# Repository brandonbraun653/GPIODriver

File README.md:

# GPIODriver

This project is intended to provide a low-cost USB tethered HW/SW solution for controlling a large amount of discrete IO
signals at standard aircraft voltage levels (28vdc). More will be added here as the project matures. Currently in the
prototyping phase for both the hardware and the software.

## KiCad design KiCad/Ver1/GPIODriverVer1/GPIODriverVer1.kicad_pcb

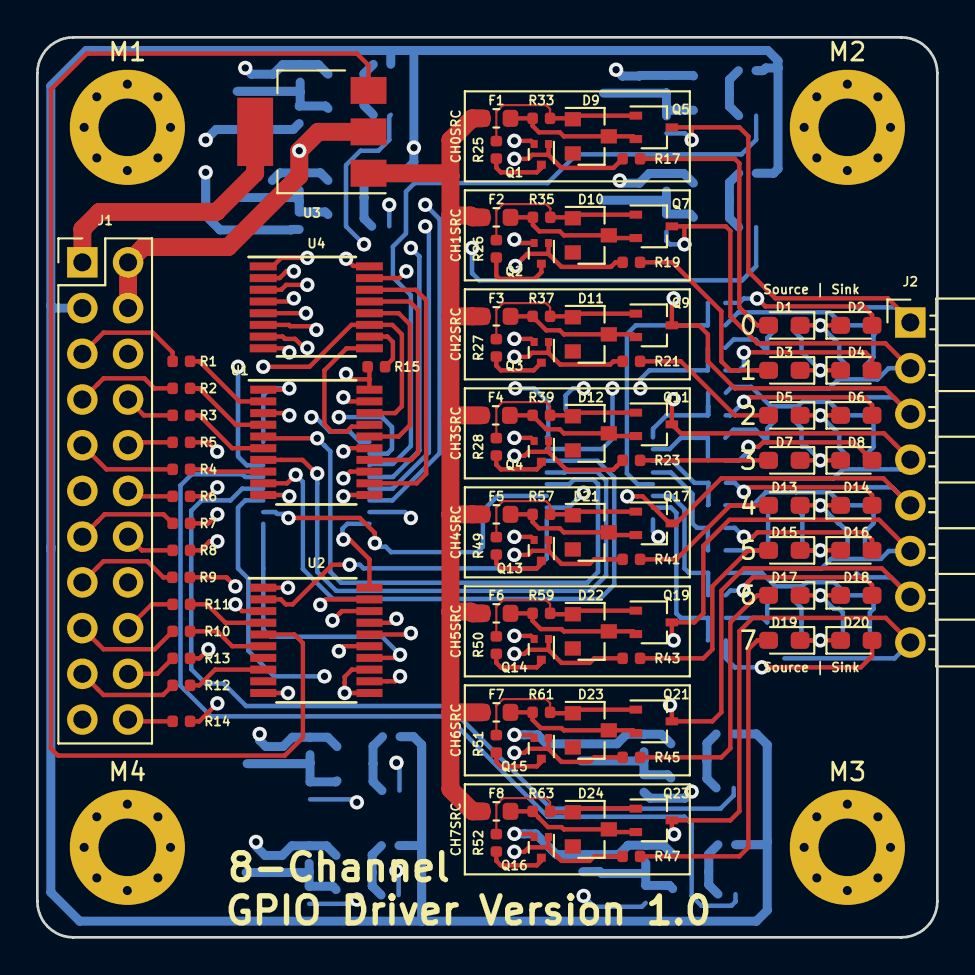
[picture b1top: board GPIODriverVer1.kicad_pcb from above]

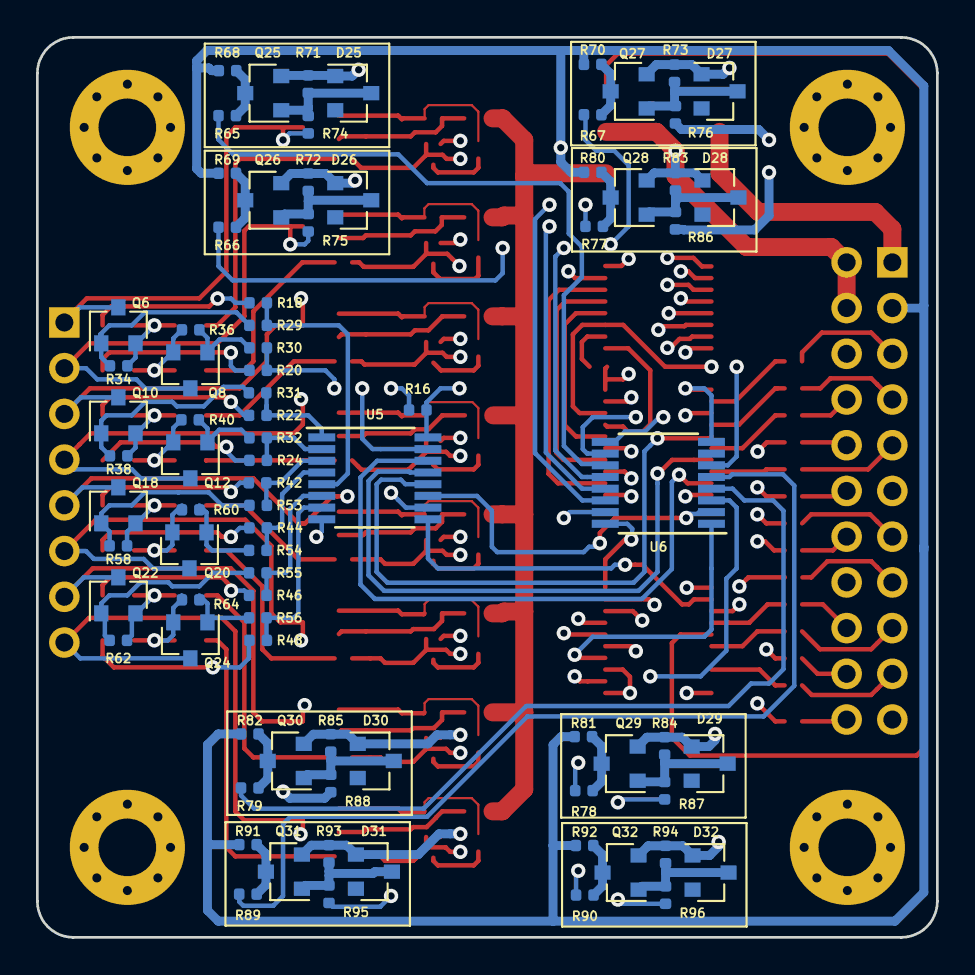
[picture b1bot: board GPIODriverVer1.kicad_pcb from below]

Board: 4 copper layers, 50.0 x 50.0 mm, 180 parts (83 on the bottom side), 144 nets.

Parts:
D1, D3, D5, D7, D13, D15, D17, D19: ActiveSource; D_0603_1608Metric_Pad1.05x0.95mm_HandSolder
D2, D4, D6, D8, D14, D16, D18, D20: ActiveSink; D_0603_1608Metric_Pad1.05x0.95mm_HandSolder
D9, D10, D11, D12, D21, D22, D23, D24, D25, D26, D27, D28, D29, D30, D31, D32: BZX84C12; D_SOT-23_ANK
F1, F2, F3, F4, F5, F6, F7, F8: C2Q300; R_0603_1608Metric
J1: Conn_01x22_Male; PinHeader_2x11_P2.54mm_Vertical
J2: GPIODriveOutputs; PinHeader_1x08_P2.54mm_Horizontal
M1, M2, M3, M4: MountingHole_3.2mm_M3_Pad_Via
Q1, Q2, Q3, Q4, Q13, Q14, Q15, Q16: DTC143EE; SOT-723
Q5, Q7, Q9, Q11, Q17, Q19, Q21, Q23: BSS84; SOT-323_SC-70
Q6, Q8, Q10, Q12, Q18, Q20, Q22, Q24, Q25, Q26, Q27, Q28, Q29, Q30, Q31, Q32: 2N7002; SOT-23
R1, R2, R3, R4, R5, R6, R7, R8, R9, R10, R11, R12, R13, R14, R29, R30, R31, R32, R53, R54, R55, R56, R65, R66, R67, R77, R78, R79, R89, R90: 100; R_0402_1005Metric
R15, R16, R33, R34, R35, R36, R37, R38, R39, R40, R57, R58, R59, R60, R61, R62, R63, R64, R71, R72, R73, R83, R84, R85, R93, R94: 10k; R_0402_1005Metric
R17, R18, R19, R20, R21, R22, R23, R24, R41, R42, R43, R44, R45, R46, R47, R48, R68, R69, R70, R74, R75, R76, R80, R81, R82, R86, R87, R88, R91, R92, R95, R96: 1k; R_0402_1005Metric
R25, R26, R27, R28, R49, R50, R51, R52: 400; R_0402_1005Metric
U1, U2: 74HC244; TSSOP-20_4.4x6.5mm_P0.65mm
U3: NCV8452; SOT-223
U4, U5: 74HC595_Nexperia; TSSOP-16_4.4x5mm_P0.65mm
U6: 74HC165; TSSOP-16_4.4x5mm_P0.65mm

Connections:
/DriveSense/D0_In: J2.1, Q5.3, Q6.3, R74.1
/DriveSense/D0_Out: R65.2, U6.11
/DriveSense/D1_In: J2.2, Q7.3, Q8.3, R75.1
/DriveSense/D1_Out: R66.2, U6.12
/DriveSense/D2_In: J2.3, Q9.3, Q10.3, R76.1
/DriveSense/D2_Out: R67.2, U6.13
/DriveSense/D3_In: J2.4, Q11.3, Q12.3, R86.1
/DriveSense/D3_Out: R77.2, U6.14
/DriveSense/D4_In: J2.5, Q17.3, Q18.3, R87.1
/DriveSense/D4_Out: R78.2, U6.3
/DriveSense/D5_In: J2.6, Q19.3, Q20.3, R88.1
/DriveSense/D5_Out: R79.2, U6.4
/DriveSense/D6_In: J2.7, Q21.3, Q22.3, R95.1
/DriveSense/D6_Out: R89.2, U6.5
/DriveSense/D7_In: J2.8, Q23.3, Q24.3, R96.1
/DriveSense/D7_Out: R90.2, U6.6
/OutputDrive/D0_Sink: R18.2, R29.2, U5.5
/OutputDrive/D0_Source: Q1.1, R17.2, U4.15
/OutputDrive/D1_Sink: R20.2, R30.2, U5.15
/OutputDrive/D1_Source: Q2.1, R19.2, U4.1
/OutputDrive/D2_Sink: R22.2, R31.2, U5.1
/OutputDrive/D2_Source: Q3.1, R21.2, U4.2
/OutputDrive/D3_Sink: R24.2, R32.2, U5.2
/OutputDrive/D3_Source: Q4.1, R23.2, U4.3
/OutputDrive/D4_Sink: R42.2, R53.2, U5.3
/OutputDrive/D4_Source: Q13.1, R41.2, U4.4
/OutputDrive/D5_Sink: R44.2, R54.2, U5.4
/OutputDrive/D5_Source: Q14.1, R43.2, U4.5
/OutputDrive/D6_Sink: R46.2, R55.2, U5.6
/OutputDrive/D6_Source: Q15.1, R45.2, U4.6
/OutputDrive/D7_Sink: R48.2, R56.2, U5.7
/OutputDrive/D7_Source: Q16.1, R47.2, U4.7
GND: D1.1, D2.1, D3.1, D4.1, D5.1, D6.1, D7.1, D8.1, D13.1, D14.1, D15.1, D16.1, D17.1, D18.1, D19.1, D20.1, D25.2, D26.2, D27.2, D28.2, D29.2, D30.2, D31.2, D32.2, J1.2, J1.4, J1.6, J1.11, J1.16, J1.21, Q1.2, Q2.2, Q3.2, Q4.2, Q6.2, Q8.2, Q10.2, Q12.2, Q13.2, Q14.2, Q15.2, Q16.2, Q18.2, Q20.2, Q22.2, Q24.2, Q25.2, Q26.2, Q27.2, Q28.2, Q29.2, Q30.2, Q31.2, Q32.2, R34.1, R36.1, R38.1, R40.1, R58.1, R60.1, R62.1, R64.1, R71.2, R72.2, R73.2, R83.2, R84.2, R85.2, R93.2, R94.2, U1.1, U1.10, U1.19, U2.1, U2.10, U2.11, U2.13, U2.19, U3.2, U4.8, U5.8, U6.8
GPIO_CLK: R1.1, U1.2
GPIO_PWR_EN: R14.1, U2.15
GPIO_Sense_CS: R11.1, U2.4
GPIO_Sense_DI: R12.1, U2.8
GPIO_Sense_DO: R13.1, U2.3
GPIO_Sense_Load: R10.1, U2.6
GPIO_Sink_DI: R8.1, U1.11
GPIO_Sink_DO: R9.1, U2.18
GPIO_Sink_LAT: R6.1, U1.15
GPIO_Sink_OE: R7.1, U1.13
GPIO_Source_DI: R4.1, U1.8
GPIO_Source_DO: R5.1, U1.3
GPIO_Source_LAT: R2.1, U1.4
GPIO_Source_OE: R3.1, U1.6
unnamed: D1.2, R17.1
unnamed: D2.2, R18.1
unnamed: D3.2, R19.1
unnamed: D4.2, R20.1
unnamed: D5.2, R21.1
unnamed: D6.2, R22.1
unnamed: D7.2, R23.1
unnamed: D8.2, R24.1
unnamed: D9.1, F1.2, Q5.2, R33.1
unnamed: D9.2, Q5.1, R25.2, R33.2
unnamed: D10.1, F2.2, Q7.2, R35.1
unnamed: D10.2, Q7.1, R26.2, R35.2
unnamed: D11.1, F3.2, Q9.2, R37.1
unnamed: D11.2, Q9.1, R27.2, R37.2
unnamed: D12.1, F4.2, Q11.2, R39.1
unnamed: D12.2, Q11.1, R28.2, R39.2
unnamed: D13.2, R41.1
unnamed: D14.2, R42.1
unnamed: D15.2, R43.1
unnamed: D16.2, R44.1
unnamed: D17.2, R45.1
unnamed: D18.2, R46.1
unnamed: D19.2, R47.1
unnamed: D20.2, R48.1
unnamed: D21.1, F5.2, Q17.2, R57.1
unnamed: D21.2, Q17.1, R49.2, R57.2
unnamed: D22.1, F6.2, Q19.2, R59.1
unnamed: D22.2, Q19.1, R50.2, R59.2
unnamed: D23.1, F7.2, Q21.2, R61.1
unnamed: D23.2, Q21.1, R51.2, R61.2
unnamed: D24.1, F8.2, Q23.2, R63.1
unnamed: D24.2, Q23.1, R52.2, R63.2
unnamed: D25.1, Q25.1, R71.1, R74.2
unnamed: D26.1, Q26.1, R72.1, R75.2
unnamed: D27.1, Q27.1, R73.1, R76.2
unnamed: D28.1, Q28.1, R83.1, R86.2
unnamed: D29.1, Q29.1, R84.1, R87.2
unnamed: D30.1, Q30.1, R85.1, R88.2
unnamed: D31.1, Q31.1, R93.1, R95.2
unnamed: D32.1, Q32.1, R94.1, R96.2
unnamed: J1.5, R1.2
unnamed: J1.7, R2.2
unnamed: J1.8, R3.2
unnamed: J1.9, R4.2
unnamed: J1.10, R5.2
unnamed: J1.12, R6.2
unnamed: J1.13, R7.2
unnamed: J1.14, R8.2
unnamed: J1.15, R9.2
unnamed: J1.17, R10.2
unnamed: J1.18, R11.2
unnamed: J1.19, R12.2
unnamed: J1.20, R13.2
unnamed: J1.22, R14.2
unnamed: Q1.3, R25.1
unnamed: Q2.3, R26.1
unnamed: Q3.3, R27.1
unnamed: Q4.3, R28.1
unnamed: Q6.1, R29.1, R34.2
unnamed: Q8.1, R30.1, R36.2
unnamed: Q10.1, R31.1, R38.2
unnamed: Q12.1, R32.1, R40.2
unnamed: Q13.3, R49.1
unnamed: Q14.3, R50.1
unnamed: Q15.3, R51.1
unnamed: Q16.3, R52.1
unnamed: Q18.1, R53.1, R58.2
unnamed: Q20.1, R54.1, R60.2
unnamed: Q22.1, R55.1, R62.2
unnamed: Q24.1, R56.1, R64.2
unnamed: Q25.3, R65.1, R68.2
unnamed: Q26.3, R66.1, R69.2
unnamed: Q27.3, R67.1, R70.2
unnamed: Q28.3, R77.1, R80.2
unnamed: Q29.3, R78.1, R81.2
unnamed: Q30.3, R79.1, R82.2
unnamed: Q31.3, R89.1, R91.2
unnamed: Q32.3, R90.1, R92.2
unnamed: R15.1, U4.10
unnamed: R16.1, U5.10
PowerEnable: U2.5, U3.3
SR_CLK: U1.18, U4.11, U5.11, U6.2
SenseDriver_CS: U2.16, U6.15
SenseDriver_DataIn: U2.12, U6.10
SenseDriver_DataOut: U2.17, U6.9
SenseDriver_Load: U2.14, U6.1
SinkDriver_DataIn: U1.9, U5.14
SinkDriver_DataOut: U2.2, U5.9
SinkDriver_LAT: U1.5, U5.12
SinkDriver_OE: U1.7, U5.13
SrcDriver_DataIn: U1.12, U4.14
SrcDriver_DataOut: U1.17, U4.9
SrcDriver_LAT: U1.16, U4.12
SrcDriver_OE: U1.14, U4.13
V+: J1.1, U3.4
VCC: J1.3, R15.2, R16.2, R68.1, R69.1, R70.1, R80.1, R81.1, R82.1, R91.1, R92.1, U1.20, U2.20, U4.16, U5.16, U6.16
VDrive: F1.1, F2.1, F3.1, F4.1, F5.1, F6.1, F7.1, F8.1, U3.1

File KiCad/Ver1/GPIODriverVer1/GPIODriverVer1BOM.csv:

Id,Designator,Package,Quantity,Designation,Supplier and ref
1,"M4,M3,M1,M2",MountingHole_3.2mm_M3_Pad_Via,4,MountingHole_3.2mm_M3_Pad_Via,
2,"Q23,Q21,Q19,Q17,Q11,Q9,Q7,Q5",SOT-323_SC-70,8,BSS84,
3,J1,PinHeader_2x11_P2.54mm_Vertical,1,Conn_01x22_Male,
4,"D1,D3,D5,D7,D13,D15,D17,D19",D_0603_1608Metric_Pad1.05x0.95mm_HandSolder,8,ActiveSource,
5,"D2,D4,D6,D8,D14,D16,D18,D20",D_0603_1608Metric_Pad1.05x0.95mm_HandSolder,8,ActiveSink,
6,"D9,D10,D11,D12,D21,D22,D23,D24,D25,D26,D27,D28,D29,D30,D31,D32",D_SOT-23_ANK,16,BZX84C12,
7,"F1,F2,F3,F4,F5,F6,F7,F8",R_0603_1608Metric,8,C2Q300,
8,J2,PinHeader_1x08_P2.54mm_Horizontal,1,GPIODriveOutputs,
9,"Q1,Q2,Q3,Q4,Q13,Q14,Q15,Q16",SOT-723,8,DTC143EE,
10,"Q6,Q8,Q10,Q12,Q18,Q20,Q22,Q24,Q25,Q26,Q27,Q28,Q29,Q30,Q31,Q32",SOT-23,16,2N7002,
11,"R1,R2,R3,R4,R5,R6,R7,R8,R9,R10,R11,R12,R13,R14,R29,R30,R31,R32,R53,R54,R55,R56,R65,R66,R67,R77,R78,R79,R89,R90",R_0402_1005Metric,30,100,
12,"R15,R16,R33,R34,R35,R36,R37,R38,R39,R40,R57,R58,R59,R60,R61,R62,R63,R64,R71,R72,R73,R83,R84,R85,R93,R94",R_0402_1005Metric,26,10k,
13,"R17,R18,R19,R20,R21,R22,R23,R24,R41,R42,R43,R44,R45,R46,R47,R48,R68,R69,R70,R74,R75,R76,R80,R81,R82,R86,R87,R88,R91,R92,R95,R96",R_0402_1005Metric,32,1k,
14,"R25,R26,R27,R28,R49,R50,R51,R52",R_0402_1005Metric,8,400,
15,"U1,U2",TSSOP-20_4.4x6.5mm_P0.65mm,2,74HC244,
16,U3,SOT-223,1,NCV8452,
17,"U4,U5",TSSOP-16_4.4x5mm_P0.65mm,2,74HC595_Nexperia,
18,U6,TSSOP-16_4.4x5mm_P0.65mm,1,74HC165,

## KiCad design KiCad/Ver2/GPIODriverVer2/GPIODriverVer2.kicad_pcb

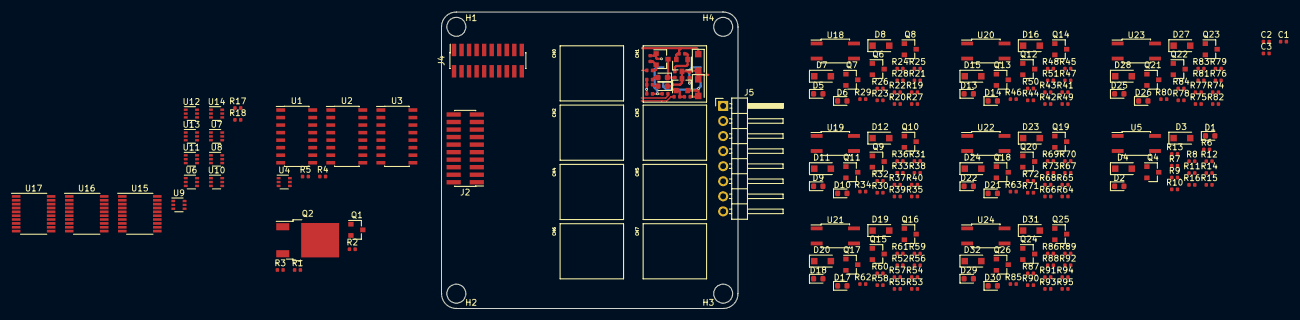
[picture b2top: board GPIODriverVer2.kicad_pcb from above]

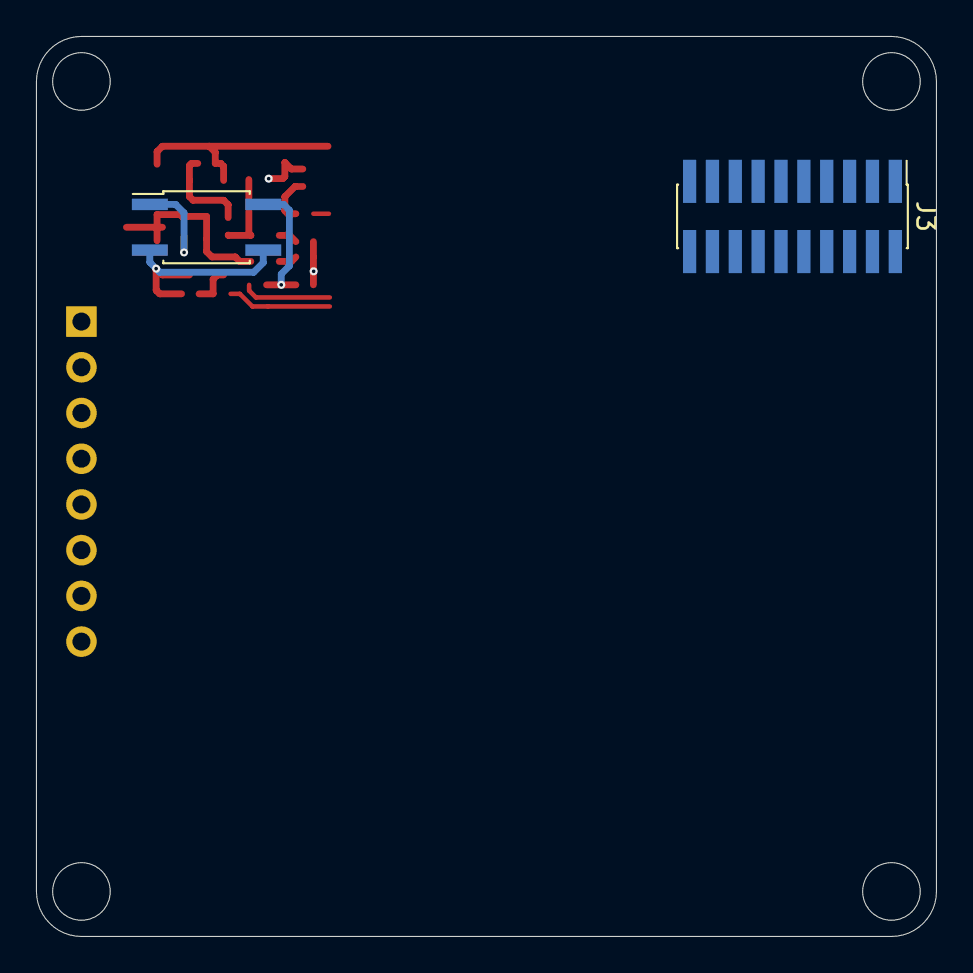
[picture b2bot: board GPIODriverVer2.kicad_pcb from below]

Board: 4 copper layers, 50.0 x 50.0 mm, 205 parts (2 on the bottom side), 113 nets.

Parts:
C1, C2, C3: 100nF; C_0402_1005Metric
D1, D1#2, D5, D9, D13, D17, D21, D25, D29: LED_HI_DRIVE_EN; D_0603_1608Metric
D2, D2#2, D6, D10, D14, D18, D22, D26, D30: LED_LO_DRIVE_EN; D_0603_1608Metric
D3, D3#2, D4, D4#2, D7, D8, D11, D12, D15, D16, D19, D20, D23, D24, D27, D28, D31, D32: 1N4007; D_SOD-123F
H1, H2, H3, H4: MountingHole_Pad; MountingHole_3.2mm_M3
J2: ExtInputs; PinHeader_2x10_P1.27mm_Vertical_SMD
J3: DaisyChainInput; PinHeader_2x10_P1.27mm_Vertical_SMD
J4: DaisyChainOutput; PinSocket_2x10_P1.27mm_Vertical_SMD
J5: DriveOutput; PinHeader_1x08_P2.54mm_Horizontal
Q1, Q3, Q6, Q9, Q12, Q15, Q18, Q21, Q24: 2N3904; SOT-23
Q2: AOD409; TO-252-2
Q4, Q4#2, Q7, Q10, Q13, Q16, Q19, Q22, Q25: MMBT5401; SOT-23
Q5, Q8, Q11, Q14, Q17, Q20, Q23, Q26: MMBT5551L; SOT-23
R1, R7, R7#2, R9, R9#2, R13, R13#2, R20, R22, R26, R31, R33, R37, R42, R44, R48, R53, R55, R59, R64, R66, R70, R75, R77, R81, R86, R88, R92: 100; R_0402_1005Metric
R2, R3, R4, R5, R8, R8#2, R10, R10#2, R14, R14#2, R15, R15#2, R17, R18, R21, R23, R27, R28, R32, R34, R38, R39, R43, R45, R49, R50, R54, R56, R60, R61, R65, R67, R71, R72, R76, R78, R82, R83, R87, R89, R93, R94: 10k; R_0402_1005Metric
R6, R6#2, R12, R12#2, R19, R25, R30, R36, R41, R47, R52, R58, R63, R69, R74, R80, R85, R91: 1.8k; R_0402_1005Metric
R11, R11#2, R24, R35, R46, R57, R68, R79, R90: 500; R_0402_1005Metric
R16, R16#2, R29, R40, R51, R62, R73, R84, R95: 5.6k; R_0402_1005Metric
U1: SR_WRITE_HI; SOIC-16_3.9x9.9mm_P1.27mm
U2: SR_WRITE_LO; SOIC-16_3.9x9.9mm_P1.27mm
U3: SR_READ_STATE; SOIC-16_3.9x9.9mm_P1.27mm
U4, U6, U7, U8, U9, U10, U11, U12, U13, U14: 74LVC1G3157; SOT-363_SC-70-6
U5, U5#2, U18, U19, U20, U21, U22, U23, U24: LTV-357T; SO-4_4.4x3.6mm_P2.54mm
U15, U16, U17: 74HC244; TSSOP-20_4.4x6.5mm_P0.65mm

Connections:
/DriveCircuitry/DriveChannel0/DriveOutput: D30.1, D31.2, D32.1, J5.1, Q25.3, Q26.3, R95.2
/DriveCircuitry/DriveChannel1/DriveOutput: D2.1, D2#2.1, D3.2, D3#2.2, D4.1, D4#2.1, J5.2, Q4.3, Q4#2.3, Q5.3, R16.2, R16#2.2
/DriveCircuitry/DriveChannel2/DriveOutput: D6.1, D7.2, D8.1, J5.3, Q7.3, Q8.3, R29.2
/DriveCircuitry/DriveChannel3/DriveOutput: D10.1, D11.2, D12.1, J5.4, Q10.3, Q11.3, R40.2
/DriveCircuitry/DriveChannel4/DriveOutput: D14.1, D15.2, D16.1, J5.5, Q13.3, Q14.3, R51.2
/DriveCircuitry/DriveChannel5/DriveOutput: D18.1, D19.2, D20.1, J5.6, Q16.3, Q17.3, R62.2
/DriveCircuitry/DriveChannel6/DriveOutput: D22.1, D23.2, D24.1, J5.7, Q19.3, Q20.3, R73.2
/DriveCircuitry/DriveChannel7/DriveOutput: D26.1, D27.2, D28.1, J5.8, Q22.3, Q23.3, R84.2
/InputCircuitry/EXT_3V3_PWR: J4.13, J4.15
/InputCircuitry/EXT_5V_PWR: J4.1, J4.3
/InputCircuitry/EXT_HV_PWR: J4.7, J4.9
/InputCircuitry/INT_OUTPUT_DRIVE_EN: U1.13, U2.13
/InputCircuitry/INT_SPI_RW_MOSI: U1.14, U2.14
/InputCircuitry/INT_SPI_RW_SCK: U1.11, U2.11, U3.2
/InputCircuitry/INT_SPI_W_CS_HI_DRIVE: U1.12, U4.6
CH0_HI_EN: R86.2, U1.15
CH0_LO_EN: R92.2, U2.15
CH0_STATE: R88.2, U3.11
CH1_HI_EN: R7.2, R7#2.2, U1.1
CH1_LO_EN: R13.2, R13#2.2, U2.1
CH1_STATE: R9.2, R9#2.2, U3.12
CH2_HI_EN: R20.2, U1.2
CH2_LO_EN: R26.2, U2.2
CH2_STATE: R22.2, U3.13
CH3_HI_EN: R31.2, U1.3
CH3_LO_EN: R37.2, U2.3
CH3_STATE: R33.2, U3.14
CH4_HI_EN: R42.2, U1.4
CH4_LO_EN: R48.2, U2.4
CH4_STATE: R44.2, U3.3
CH5_HI_EN: R53.2, U1.5
CH5_LO_EN: R59.2, U2.5
CH5_STATE: R55.2, U3.4
CH6_HI_EN: R64.2, U1.6
CH6_LO_EN: R70.2, U2.6
CH6_STATE: R66.2, U3.5
CH7_HI_EN: R75.2, U1.7
CH7_LO_EN: R81.2, U2.7
CH7_STATE: R77.2, U3.6
GND: C1.1, C2.1, C3.1, D4.2, D4#2.2, D8.2, D12.2, D16.2, D20.2, D24.2, D28.2, D32.2, H1.1, H2.1, H3.1, H4.1, J4.5, J4.11, J4.17, Q1.1, Q3.1, Q5.2, Q6.1, Q8.2, Q9.1, Q11.2, Q12.1, Q14.2, Q15.1, Q17.2, Q18.1, Q20.2, Q21.1, Q23.2, Q24.1, Q26.2, R3.1, R8.2, R8#2.2, R15.2, R15#2.2, R18.2, R21.2, R28.2, R32.2, R39.2, R43.2, R50.2, R54.2, R61.2, R65.2, R72.2, R76.2, R83.2, R87.2, R94.2, U1.8, U2.8, U3.8, U4.2, U5.2, U5.3, U5#2.2, U5#2.3, U6.2, U7.2, U8.2, U9.2, U10.2, U11.2, U12.2, U13.2, U14.2, U18.2, U18.3, U19.2, U19.3, U20.2, U20.3, U21.2, U21.3, U22.2, U22.3, U23.2, U23.3, U24.2, U24.3
unnamed: D1.1, D1#2.1, Q3.3, R11.2, R11#2.2
unnamed: D1.2, D1#2.2, R6.1, R6#2.1
unnamed: D2.2, D2#2.2, R12.2, R12#2.2
unnamed: D5.1, Q6.3, R24.2
unnamed: D5.2, R19.1
unnamed: D6.2, R25.2
unnamed: D9.1, Q9.3, R35.2
unnamed: D9.2, R30.1
unnamed: D10.2, R36.2
unnamed: D13.1, Q12.3, R46.2
unnamed: D13.2, R41.1
unnamed: D14.2, R47.2
unnamed: D17.1, Q15.3, R57.2
unnamed: D17.2, R52.1
unnamed: D18.2, R58.2
unnamed: D21.1, Q18.3, R68.2
unnamed: D21.2, R63.1
unnamed: D22.2, R69.2
unnamed: D25.1, Q21.3, R79.2
unnamed: D25.2, R74.1
unnamed: D26.2, R80.2
unnamed: D29.1, Q24.3, R90.2
unnamed: D29.2, R85.1
unnamed: D30.2, R91.2
unnamed: Q1.2, R1.2, R3.2
unnamed: Q1.3, Q2.2, R2.1
unnamed: Q3.2, R7.1, R7#2.1, R8.1, R8#2.1
unnamed: Q4.1, Q4#2.1, R11.1, R11#2.1, R14.2, R14#2.2
unnamed: Q5.1, R13.1, R13#2.1, R15.1, R15#2.1
unnamed: Q6.2, R20.1, R21.1
unnamed: Q7.1, R24.1, R27.2
unnamed: Q8.1, R26.1, R28.1
unnamed: Q9.2, R31.1, R32.1
unnamed: Q10.1, R35.1, R38.2
unnamed: Q11.1, R37.1, R39.1
unnamed: Q12.2, R42.1, R43.1
unnamed: Q13.1, R46.1, R49.2
unnamed: Q14.1, R48.1, R50.1
unnamed: Q15.2, R53.1, R54.1
unnamed: Q16.1, R57.1, R60.2
unnamed: Q17.1, R59.1, R61.1
unnamed: Q18.2, R64.1, R65.1
unnamed: Q19.1, R68.1, R71.2
unnamed: Q20.1, R70.1, R72.1
unnamed: Q21.2, R75.1, R76.1
unnamed: Q22.1, R79.1, R82.2
unnamed: Q23.1, R81.1, R83.1
unnamed: Q24.2, R86.1, R87.1
unnamed: Q25.1, R90.1, R93.2
unnamed: Q26.1, R92.1, R94.1
unnamed: R4.1, U2.10
unnamed: R5.1, U1.10
unnamed: R9.1, R9#2.1, R10.2, R10#2.2, U5.4, U5#2.4
unnamed: R16.1, R16#2.1, U5.1, U5#2.1
unnamed: R22.1, R23.2, U18.4
unnamed: R29.1, U18.1
unnamed: R33.1, R34.2, U19.4
unnamed: R40.1, U19.1
unnamed: R44.1, R45.2, U20.4
unnamed: R51.1, U20.1
unnamed: R55.1, R56.2, U21.4
unnamed: R62.1, U21.1
unnamed: R66.1, R67.2, U22.4
unnamed: R73.1, U22.1
unnamed: R77.1, R78.2, U23.4
unnamed: R84.1, U23.1
unnamed: R88.1, R89.2, U24.4
unnamed: R95.1, U24.1
unnamed: U1.9, U4.3
unnamed: U2.9, U4.1
SRC_SELECT: U6.6, U7.6, U8.6, U9.6, U10.6, U11.6, U12.6, U13.6, U14.6
VBUS: D3.1, D3#2.1, D7.1, D11.1, D15.1, D19.1, D23.1, D27.1, D31.1, Q2.1, Q4.2, Q4#2.2, Q7.2, Q10.2, Q13.2, Q16.2, Q19.2, Q22.2, Q25.2, R14.1, R14#2.1, R27.1, R38.1, R49.1, R60.1, R71.1, R82.1, R93.1
VCC: C1.2, C2.2, C3.2, Q2.3, R2.2, R4.2, R5.2, R6.2, R6#2.2, R10.1, R10#2.1, R12.1, R12#2.1, R17.1, R19.2, R23.1, R25.1, R30.2, R34.1, R36.1, R41.2, R45.1, R47.1, R52.2, R56.1, R58.1, R63.2, R67.1, R69.1, R74.2, R78.1, R80.1, R85.2, R89.1, R91.1, U1.16, U2.16, U3.16, U4.5, U6.5, U7.5, U8.5, U9.5, U10.5, U11.5, U12.5, U13.5, U14.5

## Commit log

2019-04-21 Added the driver ver 1 project
2019-04-21 Updated schematic to include input/output buffers. Added connections for shift registers.
2019-04-23 Save point Ver1 design.
2019-04-25 Save progress for this week
2019-05-07 Updated board with possible sink driver layout.
2019-05-09 Routed the current sink driver primitives.
2019-05-10 Fanned out/organized the sense circuit
2019-05-12 Fully routed Rev 1.0 Prototype Board
2019-05-17 Update gerbers.
2019-06-05 Added documentation generation targets and the first 'archive' as a hello world
2019-06-05 Added all the project submodules, new directories and files for tests, python api, and embedded source. Also started filling out the skeleton for the build system.
2019-06-05 Added archives folder
2019-06-05 Added new target to build the embedded executable
2019-06-06 sync
2019-06-09 Added new submodule for parsing command line args. Added many cpp files for fleshing out structure of project.
2019-06-10 Added low level hardware initialization files
2019-06-12 Added low level hardware initialization functions/threads. Created new embedded driver VisualGDB project. Submodule update.
2019-06-13 Switched the serial objects to run in interrupt mode and finished the prototype init routines.
2019-06-14 Updated development project and Thor
2019-06-15 Driver updates. Added new items to the project.
2019-06-15 Added new low level control functions.
2019-06-16 Swapped pin location of CS1. On the Nucleo board used for development, it cannot be controlled due to connected PCB components.
2019-08-26 Submodule update. Non-compile.
2019-09-02 Rebase onto Thor custom driver backend for Chimera. Barebones working serial TX with DMA.
2019-09-02 Added git version strings
2019-09-30 Submodule update
2019-09-30 Re-enabled watchdog thread after driver updates.
2020-05-14 Planned a little more of the Version 2 board.
2020-05-15 Started working on Version 2 of the PCB. Added KiCAD component library submodule.
2020-05-16 Add sheets for output drive channels.
